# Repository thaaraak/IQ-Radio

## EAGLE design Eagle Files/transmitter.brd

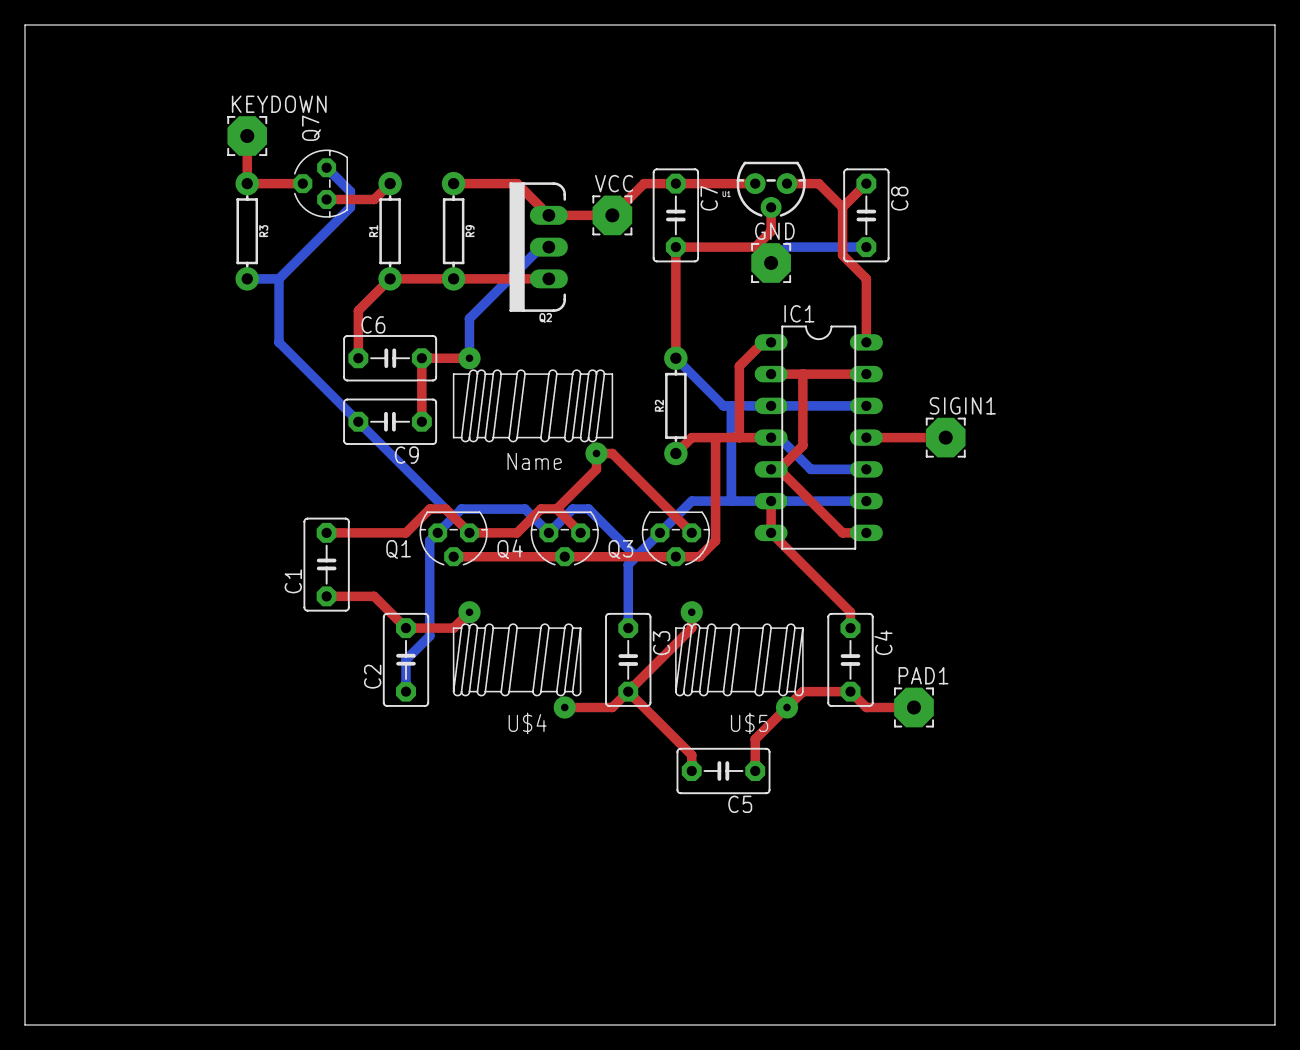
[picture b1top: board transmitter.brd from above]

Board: 2 copper layers, 100.0 x 80.0 mm, 28 parts (0 on the bottom side), 14 nets.

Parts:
C1: .1uF; C5B3.5
C2, C4: 330pF; C5B3.5
C3: 680pF; C5B3.5
C5: 68pF; C5B3.5
C6: .01uf; C5B3.5
C7: 100uF; C5B3.5
C8: 22uf; C5B3.5
C9: .1uf; C5B3.5
GND: 3,17/1,1
IC1: 7402N; DIL14
KEYDOWN: 3,17/1,1
PAD1: 3,17/1,1
Q1, Q3, Q4: BS170; TO92
Q2: 24A/20V/50mΩ; TO220V
Q7: 2N7000TO92WIDE; TO92
R1: 47k; AXIAL-0.3
R2, R9: 100k; AXIAL-0.3
R3: 10k; AXIAL-0.3
SIGIN1: 3,17/1,1
U1: TO-92
U$3: T50_INDUCTOR
U$4, U$5: T37_INDUCTOR
VCC: 3,17/1,1

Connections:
5V: C8.1, IC1.14, U1.1
GND: C2.1, C3.1, C4.1, C7.2, C8.2, C9.2, GND.1, IC1.3, IC1.6, IC1.7, IC1.9, IC1.12, Q1.1, Q3.1, Q4.1, Q7.1, R2.P$2, R3.P$2, U1.2
unnamed: C1.1, C2.2, U$4.CB
unnamed: C1.2, Q1.3, Q3.3, Q4.3, U$3.CA
unnamed: C6.2, C9.1, Q2.2, U$3.CB
unnamed: C6.1, Q2.1, R1.P$1, R9.P$2
unnamed: Q7.3, R1.P$2
unnamed: IC1.2, IC1.5, IC1.8, IC1.13
unnamed: KEYDOWN.1, Q7.2, R3.P$1
unnamed: IC1.1, IC1.4, IC1.10, Q1.2, Q3.2, Q4.2, R2.P$1
unnamed: IC1.11, SIGIN1.1
unnamed: C3.2, C5.2, U$4.CA, U$5.CB
unnamed: C4.2, C5.1, PAD1.1, U$5.CA
VCC: C7.1, Q2.3, R9.P$1, U1.3, VCC.1

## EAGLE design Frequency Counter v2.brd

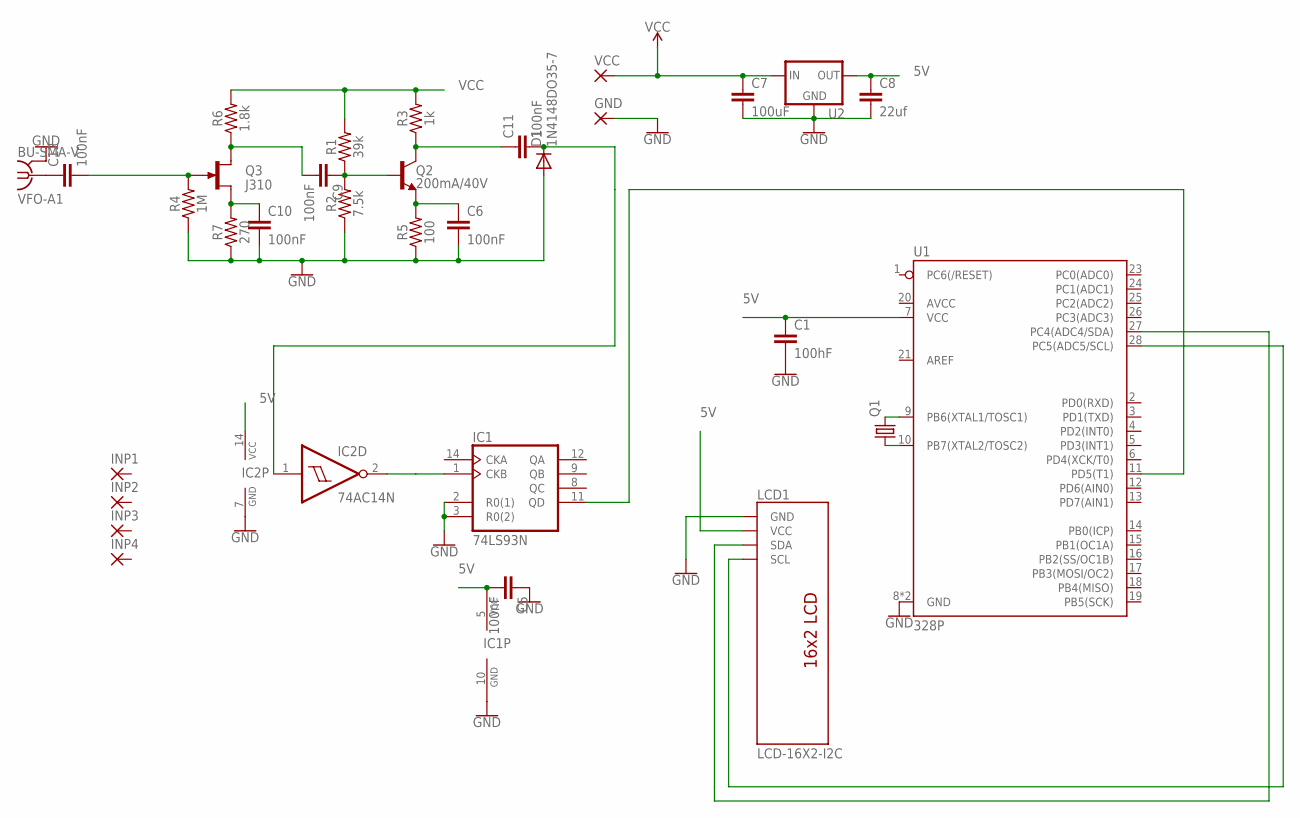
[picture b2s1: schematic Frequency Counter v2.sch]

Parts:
C1: 100hF; C5B3.5
C5, C6, C9, C10, C11, C12: 100nF; C5B3.5
C7: 100uF; C5B3.5
C8: 22uf; C5B3.5
D1: 1N4148DO35-7; DO35-7
GND: 3,17/1,1
IC1: 74LS93N; DIL14
IC2: 74AC14N; DIL14
INP1, INP2, INP3, INP4: 3,17/1,1
LCD1: LCD-16X2-I2C
Q1: CRYTALHC49S; HC49/S
Q2: 200mA/40V; TO-92
Q3: J310; TO92R
R1: 39k; AXIAL-0.3
R2: 7.5k; AXIAL-0.3
R3: 1k; AXIAL-0.3
R4: 1M; AXIAL-0.3
R5: 100; AXIAL-0.3
R6: 1.8k; AXIAL-0.3
R7: 270; AXIAL-0.3
U1: 328P; DIP28
U2: V_REG_78XXSINK; TO220-IGO
VCC: 3,17/1,1
VFO-A1: BU-SMA-V

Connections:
5V: C1.1, C5.2, C8.1, IC1.5 (VCC), IC2.14 (VCC), LCD1.2 (VCC), U1.7 (VCC), U2.OUT
GND: C1.2, C5.1, C6.2, C7.2, C8.2, C10.2, D1.A, GND.1, IC1.2 (R0(1)), IC1.3 (R0(2)), IC1.10 (GND), IC2.7 (GND), LCD1.1 (GND), R2.P$1 (1), R4.P$1 (1), R5.P$1 (1), R7.P$1 (1), U1.8 (GND), U1.22 (GND), U2.GND, VFO-A1.2, VFO-A1.3 (2), VFO-A1.4 (2), VFO-A1.5 (2)
unnamed: C12.1, VFO-A1.1
unnamed: Q1.2, U1.9 (PB6(XTAL1/TOSC1))
unnamed: Q1.1, U1.10 (PB7(XTAL2/TOSC2))
unnamed: LCD1.3 (SDA), U1.27 (PC4(ADC4/SDA))
unnamed: LCD1.4 (SCL), U1.28 (PC5(ADC5/SCL))
unnamed: C12.2, Q3.G, R4.P$2 (2)
unnamed: C9.1, Q2.2 (B), R1.P$1 (1), R2.P$2 (2)
unnamed: C9.2, Q3.D, R6.P$1 (1)
unnamed: C10.1, Q3.S, R7.P$2 (2)
unnamed: C11.2, D1.C, IC2.1 (I)
unnamed: C6.1, Q2.1 (E), R5.P$2 (2)
unnamed: C11.1, Q2.3 (C), R3.P$1 (1)
unnamed: IC1.1 (CKB), IC2.2 (O)
unnamed: IC1.11 (QD), U1.11 (PD5(T1))
VCC: C7.1, R1.P$2 (2), R3.P$2 (2), R6.P$2 (2), U2.IN, VCC.1

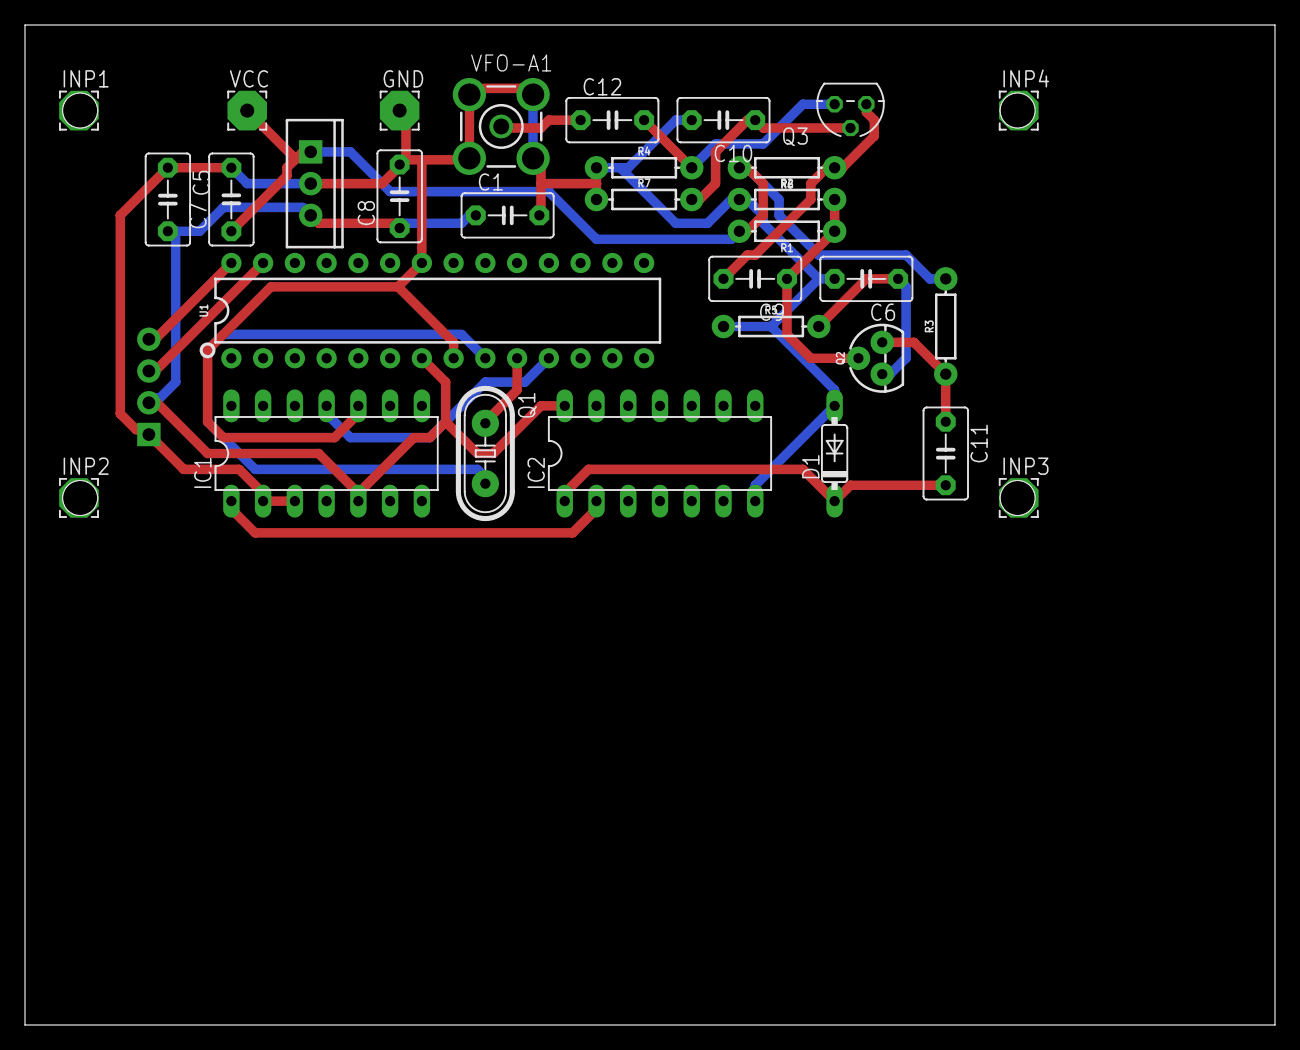
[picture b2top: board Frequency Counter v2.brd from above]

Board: 2 copper layers, 100.0 x 80.0 mm, 32 parts (1 on the bottom side), 17 nets.

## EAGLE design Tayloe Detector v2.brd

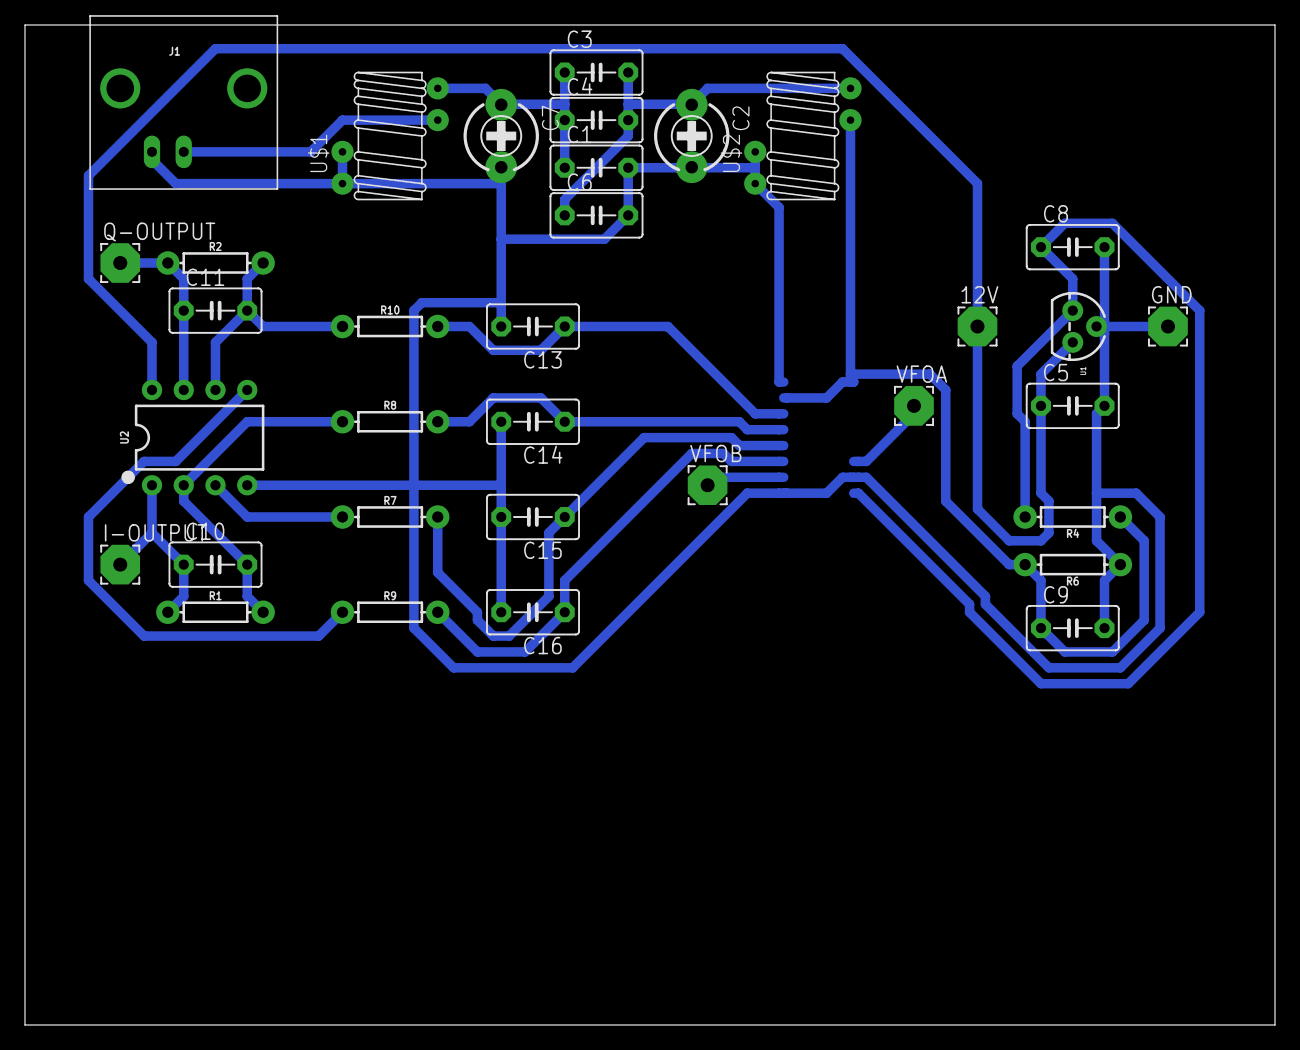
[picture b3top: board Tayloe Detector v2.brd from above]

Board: 2 copper layers, 100.0 x 80.0 mm, 35 parts (1 on the bottom side), 19 nets.

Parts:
12V: 3,17/1,1
C1, C6: 150pF; C5B3.5
C2, C7: CTRIMTZ03
C3: 10pF; C5B3.5
C4: 5pF; C5B3.5
C5: 100uF; C5B3.5
C8: 22uf; C5B3.5
C9: 22uF; C5B3.5
C10, C11: 10nF; C5B3.5
C13, C14, C15, C16: 470nF; C5B3.5
GND: 3,17/1,1
I-OUTPUT: 3,17/1,1
J1: BNCPTH; BNC
Q-OUTPUT: 3,17/1,1
R1, R2, R4, R6: 10k; AXIAL-0.3
R7, R8, R9, R10: 100; AXIAL-0.3
U1: TO-92
U2: LM358; DIP08
U$1, U$2: T37_TRANSFORMER
U$3: FST3253; SO16
VFOA: 3,17/1,1
VFOB: 3,17/1,1

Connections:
5V: C8.1, R4.P$2, U1.1, U$3.16
GND: C1.2, C2.1, C5.2, C6.2, C7.1, C8.2, C9.2, C13.2, C14.2, C15.2, C16.2, GND.1, J1.GND, R6.P$1, U1.2, U2.4, U$1.C1A, U$1.C2A, U$2.C1A, U$2.C2A, U$3.1, U$3.8, U$3.15
unnamed: R7.P$1, U2.3
unnamed: C1.1, C3.1, C4.1, C7.2, U$1.C2B
unnamed: C2.2, C3.2, C4.2, C6.1, U$2.C2B
unnamed: C9.1, R4.P$1, R6.P$2, U$2.C1B, U$3.7, U$3.9
unnamed: C10.2, R1.P$2, R8.P$1, U2.2
unnamed: J1.S, U$1.C1B
unnamed: R9.P$1, U2.5
unnamed: C10.1, I-OUTPUT.1, R1.P$1, U2.1
unnamed: C14.1, R8.P$2, U$3.5
unnamed: C11.2, R2.P$2, R10.P$1, U2.6
unnamed: C15.1, R7.P$2, U$3.4
unnamed: C13.1, R10.P$2, U$3.6
unnamed: U$3.14, VFOA.1
unnamed: C11.1, Q-OUTPUT.1, R2.P$1, U2.7
unnamed: U$3.2, VFOB.1
unnamed: C16.1, R9.P$2, U$3.3
VCC: 12V.1, C5.1, U1.3, U2.8

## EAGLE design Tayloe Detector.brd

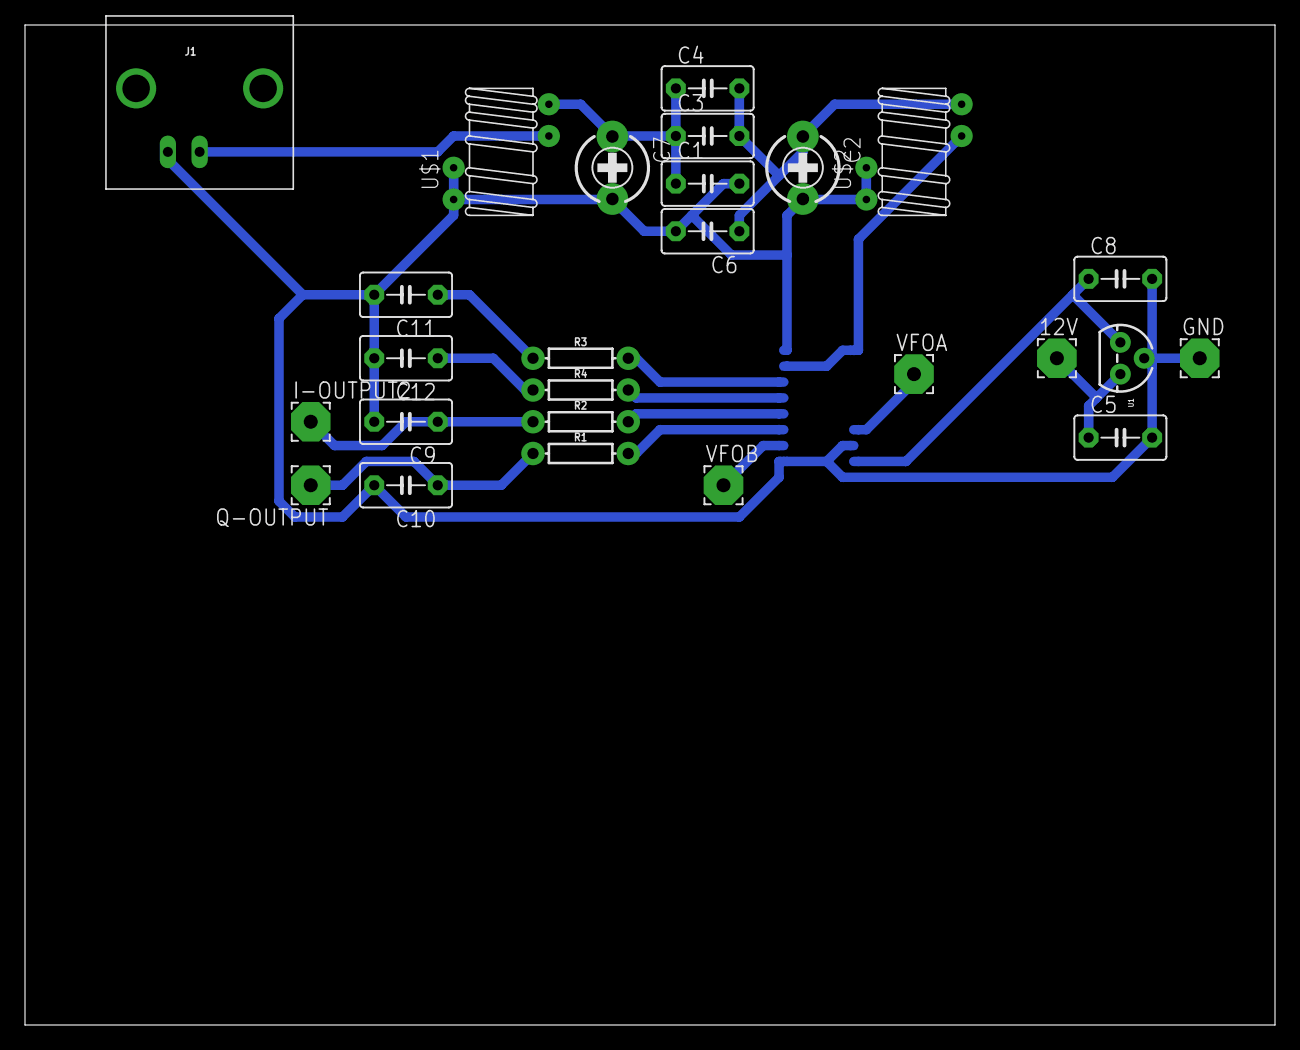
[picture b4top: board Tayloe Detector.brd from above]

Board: 2 copper layers, 100.0 x 80.0 mm, 27 parts (1 on the bottom side), 17 nets.

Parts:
12V: 3,17/1,1
C1, C6: 150pF; C5B3.5
C2, C7: CTRIMTZ03
C3: 10pF; C5B3.5
C4: 5pF; C5B3.5
C5: 100uF; C5B3.5
C8: 22uf; C5B3.5
C9, C10, C11, C12: 470nF; C5B3.5
GND: 3,17/1,1
I-OUTPUT2: 3,17/1,1
J1: BNCPTH; BNC
Q-OUTPUT: 3,17/1,1
R1, R2, R3, R4: 100; AXIAL-0.3
U1: TO-92
U$1, U$2: T37_TRANSFORMER
U$3: FST3253; SO16
VFOA: 3,17/1,1
VFOB: 3,17/1,1

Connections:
5V: C8.1, U1.1, U$3.16
GND: C1.2, C2.1, C5.2, C6.2, C7.1, C8.2, C9.2, C10.2, C11.2, C12.2, GND.1, J1.GND, U1.2, U$1.C1A, U$1.C2A, U$2.C1A, U$2.C2A, U$3.1, U$3.8, U$3.15
unnamed: C1.1, C3.1, C4.1, C7.2, U$1.C2B
unnamed: J1.S, U$1.C1B
unnamed: C2.2, C3.2, C4.2, C6.1, U$2.C2B
unnamed: U$2.C1B, U$3.7, U$3.9
unnamed: R1.P$2, U$3.3
unnamed: C10.1, Q-OUTPUT.1, R1.P$1
unnamed: C11.1, R3.P$1
unnamed: C12.1, R4.P$1
unnamed: R4.P$2, U$3.5
unnamed: C9.1, I-OUTPUT2.1, R2.P$1
unnamed: R2.P$2, U$3.4
unnamed: R3.P$2, U$3.6
unnamed: U$3.14, VFOA.1
unnamed: U$3.2, VFOB.1
VCC: 12V.1, C5.1, U1.3

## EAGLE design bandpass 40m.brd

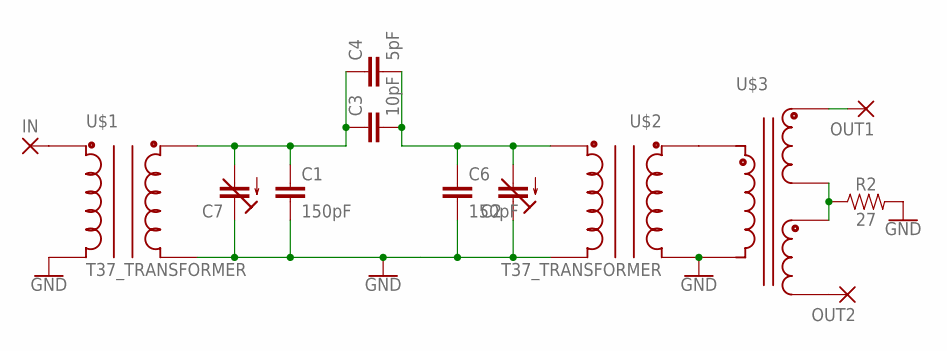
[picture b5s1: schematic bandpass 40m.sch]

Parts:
C1, C6: 150pF; C5B3.5
C2, C7: C-TRIMMTZ03; CTRIMTZ03
C3: 10pF; C5B3.5
C4: 5pF; C5B3.5
IN: 3,17/1,1
OUT1, OUT2: 3,17/1,1
R2: 27; AXIAL-0.3
U$1, U$2: T37_TRANSFORMER
U$3: T50_SPLITTER

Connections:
GND: C1.2, C2.1 (E), C6.2, C7.1 (E), R2.P$2 (2), U$1.C1A, U$1.C2A, U$2.C1A, U$2.C2A, U$3.C1A
unnamed: C1.1, C3.1, C4.1, C7.2 (A), U$1.C2B
unnamed: IN.1, U$1.C1B
unnamed: C2.2 (A), C3.2, C4.2, C6.1, U$2.C2B
unnamed: U$2.C1B, U$3.C1B
unnamed: OUT1.1, U$3.C3B (C2B)
unnamed: R2.P$1 (1), U$3.C2A (C3B), U$3.C3A (C2A)
unnamed: OUT2.1, U$3.C2B (C3A)

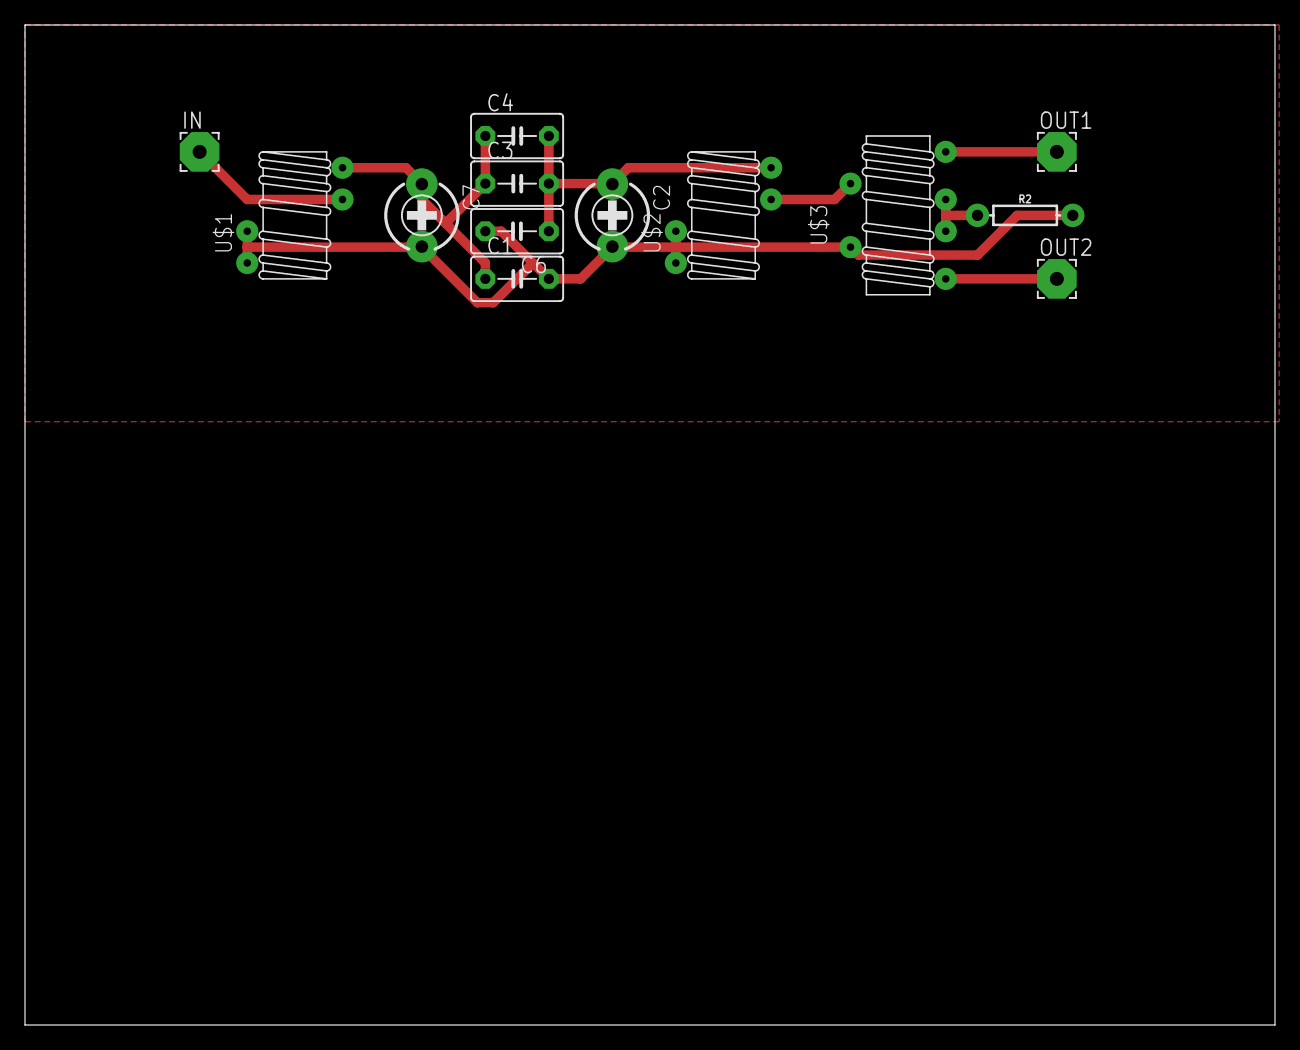
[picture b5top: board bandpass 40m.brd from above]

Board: 2 copper layers, 100.0 x 80.0 mm, 13 parts (0 on the bottom side), 8 nets.

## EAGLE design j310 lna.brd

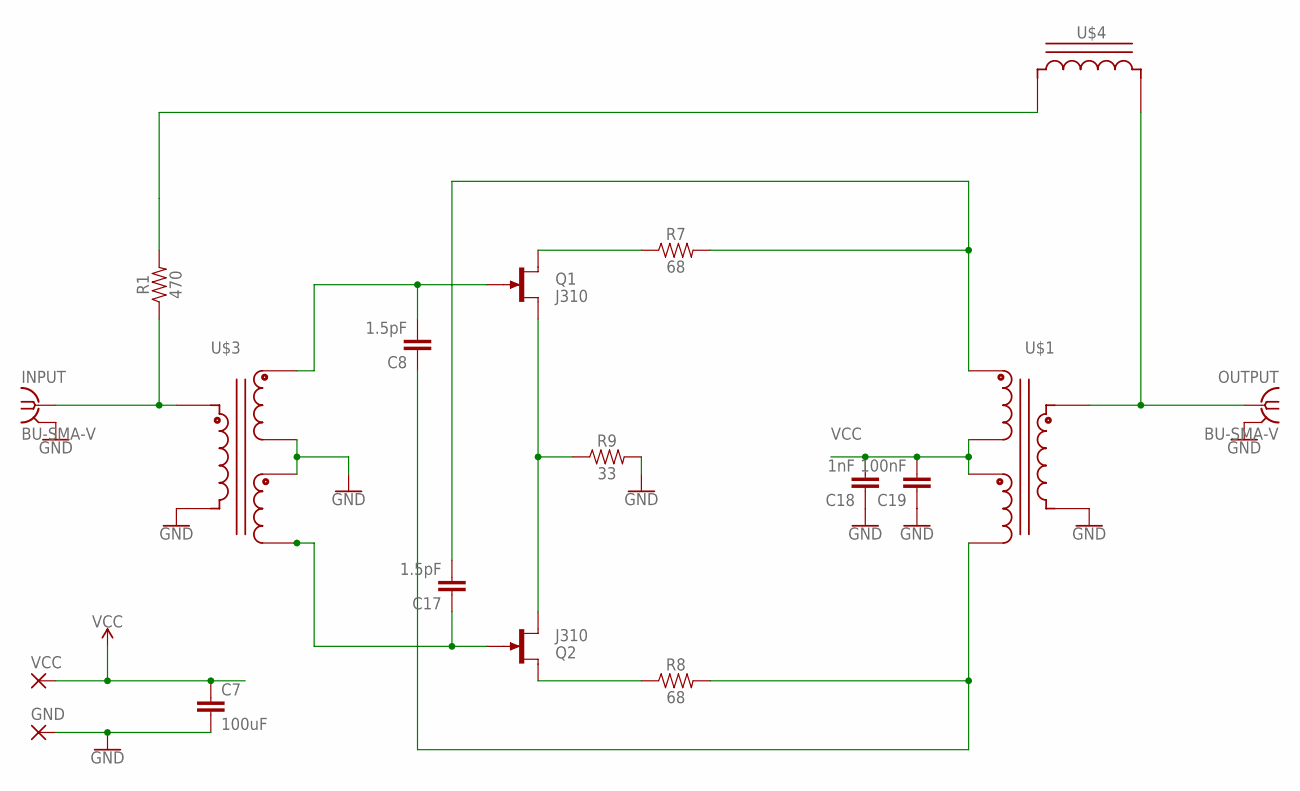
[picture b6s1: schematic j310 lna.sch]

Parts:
C7: 100uF; C5B3.5
C8, C17: 1.5pF; C5B3.5
C18: 1nF; C5B3.5
C19: 100nF; C5B3.5
GND: 3,17/1,1
INPUT: BU-SMA-V
OUTPUT: BU-SMA-V
Q1, Q2: J310; TO92R
R1: 470; AXIAL-0.3
R7, R8: 68; AXIAL-0.3
R9: 33; AXIAL-0.3
U$1, U$3: T50_SPLITTER
U$4: T37_INDUCTOR
VCC: 3,17/1,1

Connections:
GND: C7.2, C18.1, C19.1, GND.1, INPUT.2, INPUT.3 (2), INPUT.4 (2), INPUT.5 (2), OUTPUT.2, OUTPUT.3 (2), OUTPUT.4 (2), OUTPUT.5 (2), R9.P$2 (2), U$1.C1A, U$3.C1A, U$3.C2A (C3B), U$3.C3A (C2A)
unnamed: OUTPUT.1, U$1.C1B, U$4.CA
unnamed: R1.P$2 (2), U$4.CB
unnamed: Q2.D, R8.P$1 (1)
unnamed: C8.2, Q1.G, U$3.C3B (C2B)
unnamed: Q1.D, R7.P$1 (1)
unnamed: C17.1, Q2.G, U$3.C2B (C3A)
unnamed: INPUT.1, R1.P$1 (1), U$3.C1B
unnamed: Q1.S, Q2.S, R9.P$1 (1)
unnamed: C17.2, R7.P$2 (2), U$1.C3B (C2B)
unnamed: C8.1, R8.P$2 (2), U$1.C2B (C3A)
VCC: C7.1, C18.2, C19.2, U$1.C2A (C3B), U$1.C3A (C2A), VCC.1

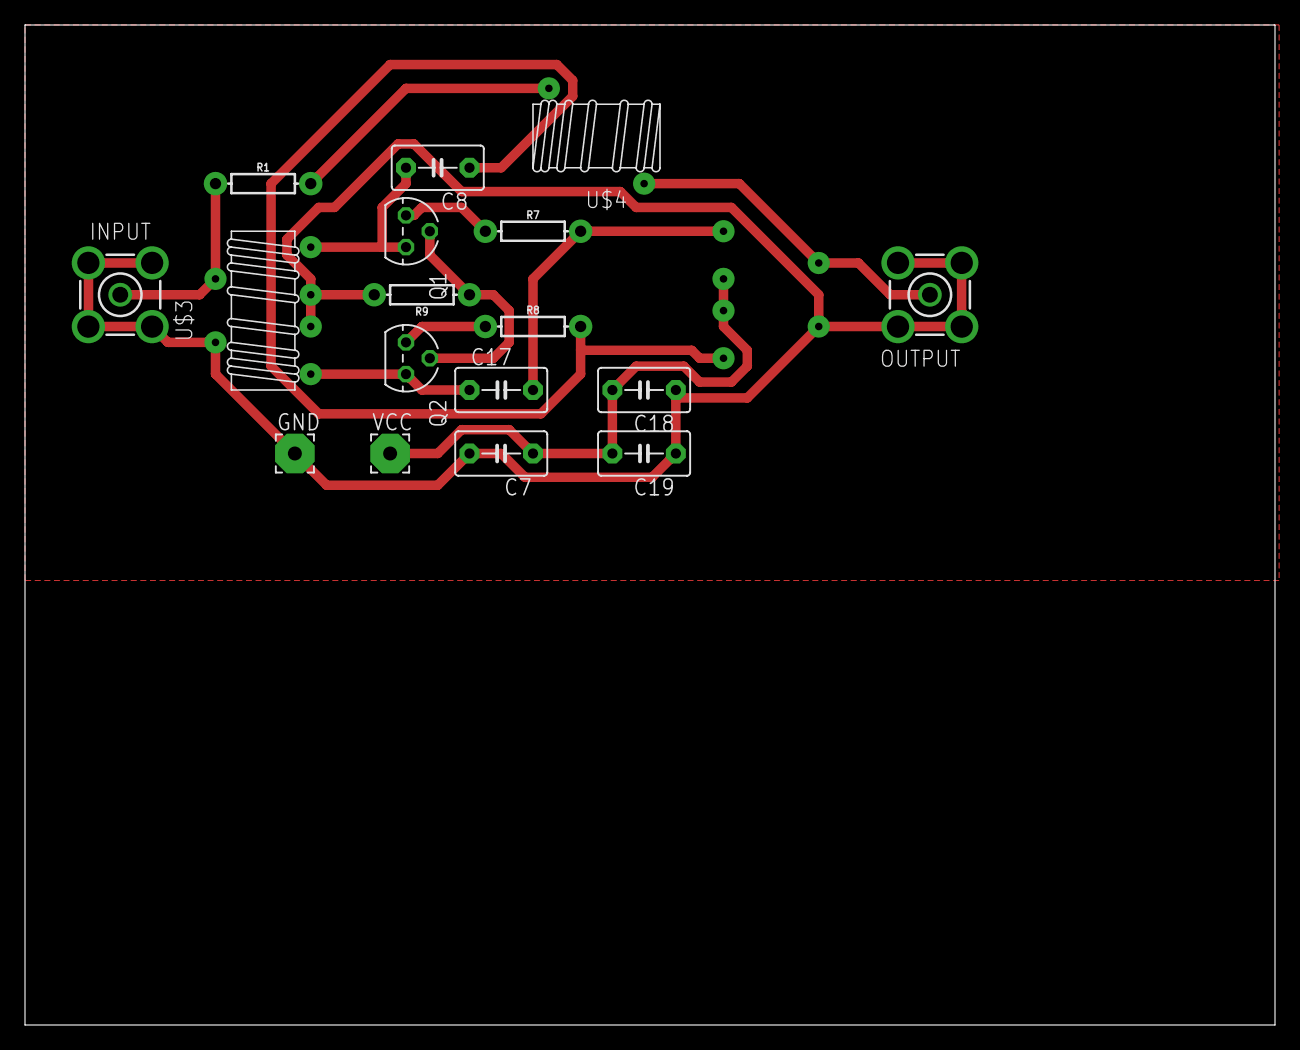
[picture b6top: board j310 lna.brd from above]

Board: 2 copper layers, 100.0 x 80.0 mm, 18 parts (1 on the bottom side), 12 nets.

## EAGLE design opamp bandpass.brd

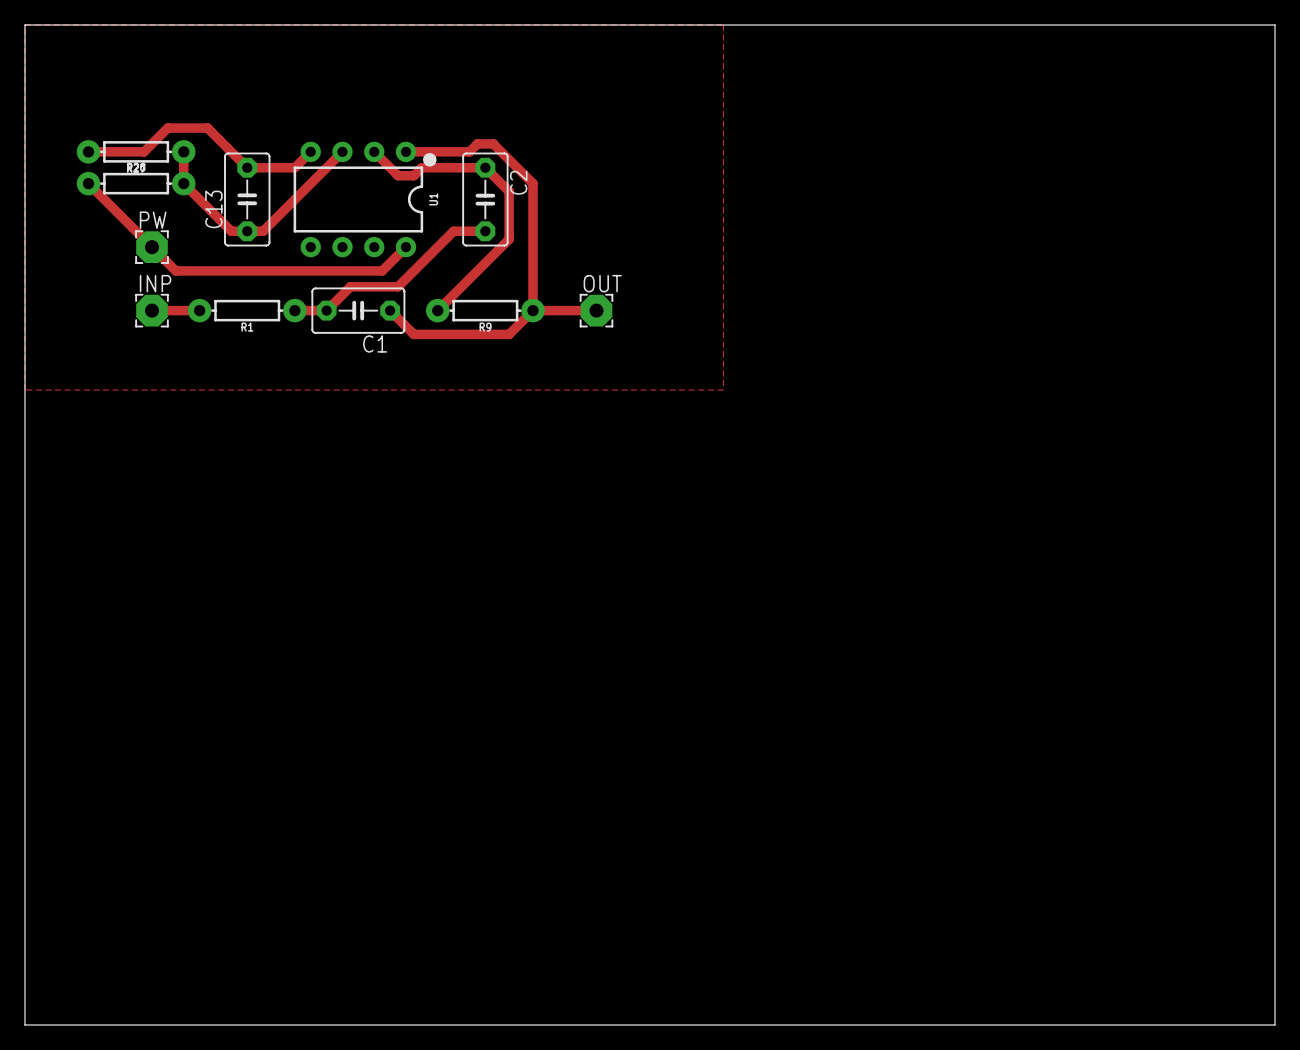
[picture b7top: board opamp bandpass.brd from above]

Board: 2 copper layers, 100.0 x 80.0 mm, 11 parts (0 on the bottom side), 7 nets.

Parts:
C1, C2: 10nF; C5B3.5
C13: 10uF; C5B3.5
INP: 2,54/1,1
OUT: 2,54/1,1
PW: 2,54/1,1
R1, R26, R27: 10k; AXIAL-0.3
R9: 20k; AXIAL-0.3
U1: LM358; DIP08

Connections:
GND: C13.2, R27.P$2, U1.4
unnamed: C1.2, C2.2, R1.P$1
unnamed: C13.1, R26.P$2, R27.P$1, U1.3
unnamed: C2.1, R9.P$2, U1.2
unnamed: INP.1, R1.P$2
unnamed: C1.1, OUT.1, R9.P$1, U1.1
VCC: PW.1, R26.P$1, U1.8

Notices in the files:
parts and their libraries:
SparkFun-IC-Power: Licensing: Creative Commons ShareAlike 4.0 International - https://creativecommons.org/licenses/by-sa/4.0
